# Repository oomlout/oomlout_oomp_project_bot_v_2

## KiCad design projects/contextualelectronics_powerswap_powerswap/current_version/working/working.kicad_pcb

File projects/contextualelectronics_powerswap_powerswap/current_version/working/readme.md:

# powerswap
 
## summary 
* id: contextualelectronics_powerswap_powerswap
* user: contextualelectronics
* name: powerswap
* board: powerswap
* repo: https://github.com/ContextualElectronics/PowerSwap
* src_file_repo_kicad_pcb: buck-boost/PowerSwap.kicad_pcb
* src_file_repo_kicad_pcb_link: https://github.com/ContextualElectronics/PowerSwap/tree/master/buck-boost/PowerSwap.kicad_pcb

* src_file_repo_brd: boost/Eagle/2015-10-22_20-31-01.brd
* src_file_repo_brd_link: https://github.com/ContextualElectronics/PowerSwap/tree/master/boost/Eagle/2015-10-22_20-31-01.brd
* src_file_repo_sch: buck-boost/PowerSwap.sch
* src_file_repo_sch_link: https://github.com/ContextualElectronics/PowerSwap/tree/master/buck-boost/PowerSwap.sch
* full details link: https://github.com/oomlout/oomlout_oomp_project_bot_v_2/tree/main/projects/contextualelectronics_powerswap_powerswap/current_version/working  

## schematic  
  
[schematic (pdf)](working_schematic.pdf) 

## pcb  

[board (pdf)](working.pdf)  

## working_bom
| Id | Designator | Footprint | Quantity | Designation | Supplier and ref |  | None | 
| --- | --- | --- | --- | --- | --- | --- | --- | 
| 1 | C1 | C_0805 | 1 | 4.7UF |  |  | [''] | 
| 2 | C2 | C_1210 | 1 | 22UF |  |  | [''] | 
| 3 | C3 | C_0805 | 1 | 0.1UF |  |  | [''] | 
| 4 | L1 | LQH3NPN2R2MM0L | 1 | 2.2uH |  |  | [''] | 
| 5 | P1,P2 | Pin_Header_Straight_1x02 | 2 | CONN_01X02 |  |  | [''] | 
| 6 | P3,P4,P5,P6 | Measurement_Point_Square-SMD-Pad_Small | 4 | TST |  |  | [''] | 
| 7 | R1 | R_0805 | 1 | 1.2M |  |  | [''] | 
| 8 | R2 | R_0805 | 1 | 215K |  |  | [''] | 
| 9 | R3,R4,R5 | R_0805 | 3 | 0 |  |  | [''] | 
| 10 | U1 | TPS63030 | 1 | TPS63030 |  |  | [''] | 
| 11 | G*** | PS_Logo | 1 | LOGO |  |  | [''] | 
| 12 | REF**1111,REF**1121,REF**1131,REF**1141,REF**1151,REF**1161,REF**1112,REF**1122,REF**1132,REF**1142,REF**1152,REF**1162,REF**1113,REF**1123,REF**1133,REF**1143,REF**1153,REF**1163,REF**1131,REF**1131,REF**1131,REF**1131,REF**1131,REF**1131,REF**1131,REF**111111,REF**111121,REF**111131,REF**111141,REF**111112,REF**111122,REF**111132,REF**111142,REF**111113,REF**111123,REF**111133,REF**111143,REF**111111,REF**111111,REF**111111,REF**111111,REF**111111,REF**111111,REF**11111111,REF**11111121,REF**11111131,REF**11111112,REF**11111122,REF**11111132,REF**11111113,REF**11111123,REF**11111133,REF**11111114,REF**11111124,REF**11111134 | VIA-0.6mm | 55 | VIA-0.6mm |  |  | [''] |

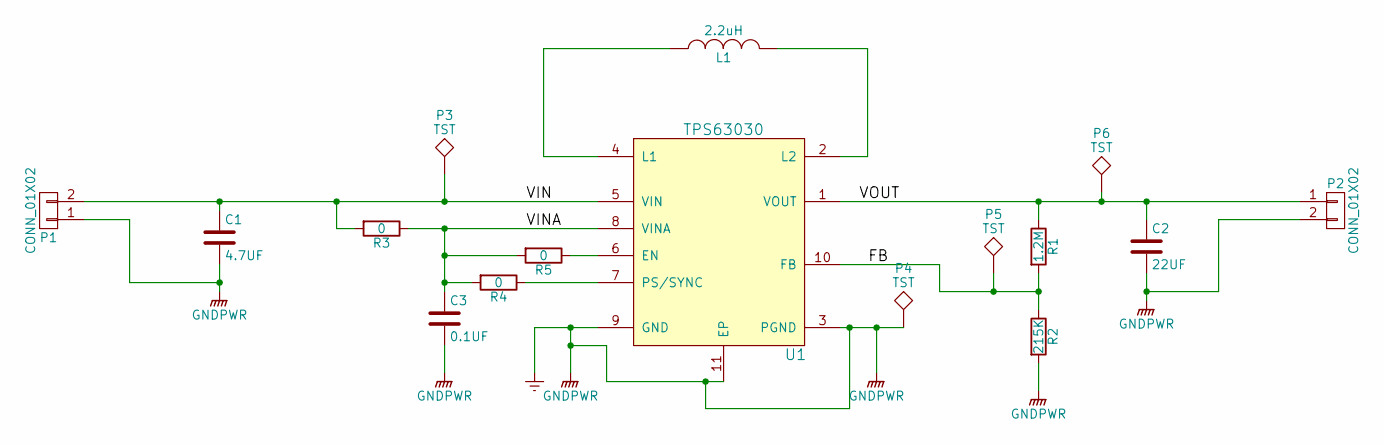
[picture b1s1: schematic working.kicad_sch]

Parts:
C1: 4.7UF; C_0805
C2: 22UF; C_1210
C3: 0.1UF; C_0805
L1: 2.2uH; LQH3NPN2R2MM0L; MPN LQH3NPN2R2MM0L
P1, P2: CONN_01X02; Pin_Header_Straight_1x02
P3, P4, P5, P6: TST; Measurement_Point_Square-SMD-Pad_Small
R1: 1.2M; R_0805
R2: 215K; R_0805
R3, R4, R5: 0; R_0805
U1: TPS63030

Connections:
/FB: P5.1, R1.2, R2.1, U1.10 (FB)
/VIN: C1.1, P1.2, P3.1, R3.2, U1.5 (VIN)
/VINA: C3.1, R3.1, R4.2, R5.2, U1.8 (VINA)
/VOUT: C2.1, P2.1, P6.1, R1.1, U1.1 (VOUT)
GNDPWR: C1.2, C2.2, C3.2, P1.1, P2.2, P4.1, R2.2, U1.3 (PGND), U1.9 (GND), U1.11 (EP)
unnamed: L1.1, U1.4 (L1)
unnamed: L1.2, U1.2 (L2)
unnamed: R4.1, U1.7 (PS/SYNC)
unnamed: R5.1, U1.6 (EN)

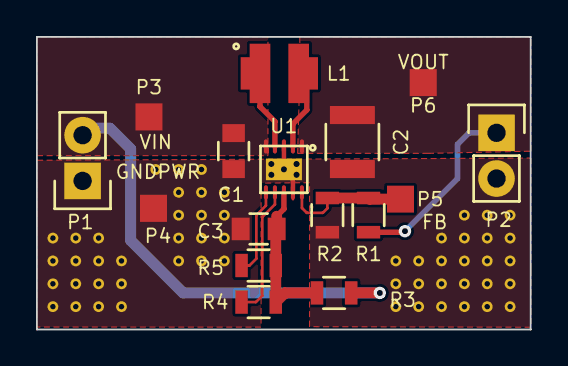
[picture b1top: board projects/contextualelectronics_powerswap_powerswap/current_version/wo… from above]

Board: 2 copper layers, 27.4 x 16.3 mm, 16 parts (0 on the bottom side), 9 nets.

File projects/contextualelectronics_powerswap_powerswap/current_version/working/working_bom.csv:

"Id";"Designator";"Footprint";"Quantity";"Designation";"Supplier and ref";
1;"C1";"C_0805";1;"4.7UF";;;
2;"C2";"C_1210";1;"22UF";;;
3;"C3";"C_0805";1;"0.1UF";;;
4;"L1";"LQH3NPN2R2MM0L";1;"2.2uH";;;
5;"P1,P2";"Pin_Header_Straight_1x02";2;"CONN_01X02";;;
6;"P3,P4,P5,P6";"Measurement_Point_Square-SMD-Pad_Small";4;"TST";;;
7;"R1";"R_0805";1;"1.2M";;;
8;"R2";"R_0805";1;"215K";;;
9;"R3,R4,R5";"R_0805";3;"0";;;
10;"U1";"TPS63030";1;"TPS63030";;;
11;"G***";"PS_Logo";1;"LOGO";;;
12;"REF**1111,REF**1121,REF**1131,REF**1141,REF**1151,REF**1161,REF**1112,REF**1122,REF**1132,REF**1142,REF**1152,REF**1162,REF**1113,REF**1123,REF**1133,REF**1143,REF**1153,REF**1163,REF**1131,REF**1131,REF**1131,REF**1131,REF**1131,REF**1131,REF**1131,REF**111111,REF**111121,REF**111131,REF**111141,REF**111112,REF**111122,REF**111132,REF**111142,REF**111113,REF**111123,REF**111133,REF**111143,REF**111111,REF**111111,REF**111111,REF**111111,REF**111111,REF**111111,REF**11111111,REF**11111121,REF**11111131,REF**11111112,REF**11111122,REF**11111132,REF**11111113,REF**11111123,REF**11111133,REF**11111114,REF**11111124,REF**11111134";"VIA-0.6mm";55;"VIA-0.6mm";;;

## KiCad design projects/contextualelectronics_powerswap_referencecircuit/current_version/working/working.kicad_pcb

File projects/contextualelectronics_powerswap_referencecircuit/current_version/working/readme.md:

# powerswap
 
## summary 
* id: contextualelectronics_powerswap_referencecircuit
* user: contextualelectronics
* name: powerswap
* board: referencecircuit
* repo: https://github.com/ContextualElectronics/PowerSwap
* src_file_repo_kicad_pcb: boost/Boost.kicad_pcb
* src_file_repo_kicad_pcb_link: https://github.com/ContextualElectronics/PowerSwap/tree/master/boost/Boost.kicad_pcb

* src_file_repo_brd: boost/Eagle/2015-10-22_20-31-01.brd
* src_file_repo_brd_link: https://github.com/ContextualElectronics/PowerSwap/tree/master/boost/Eagle/2015-10-22_20-31-01.brd
* src_file_repo_sch: boost/Boost.sch
* src_file_repo_sch_link: https://github.com/ContextualElectronics/PowerSwap/tree/master/boost/Boost.sch
* full details link: https://github.com/oomlout/oomlout_oomp_project_bot_v_2/tree/main/projects/contextualelectronics_powerswap_referencecircuit/current_version/working  

## schematic  
  
[schematic (pdf)](working_schematic.pdf) 

## pcb  

[board (pdf)](working.pdf)  

## working_bom
| Id | Designator | Footprint | Quantity | Designation | Supplier and ref |  | None | 
| --- | --- | --- | --- | --- | --- | --- | --- | 
| 1 | C1,C2,C6,C7,C8,C9 | C_1206_HandSoldering | 6 | 10U |  |  | [''] | 
| 2 | C3 | C_0805_HandSoldering | 1 | 1U |  |  | [''] | 
| 3 | C4 | C_0805_HandSoldering | 1 | 100nF |  |  | [''] | 
| 4 | C5 | C_0805_HandSoldering | 1 | 820pF |  |  | [''] | 
| 5 | D1 | SMA-SMB_Universal_Handsoldering | 1 | B340LA-13-F |  |  | [''] | 
| 6 | L1 | SRU1048 | 1 | SRU1048 |  |  | [''] | 
| 7 | P1,P2 | Pin_Header_Straight_1x02 | 2 | CONN_01X02 |  |  | [''] | 
| 8 | R1 | R_0805_HandSoldering | 1 | 57K6 |  |  | [''] | 
| 9 | R2 | R_0805_HandSoldering | 1 | 150K |  |  | [''] | 
| 10 | R3 | R_0805_HandSoldering | 1 | 39K |  |  | [''] | 
| 11 | TP1,TP2 | Measurement_Point_Square-SMD-Pad_Big | 2 | CONN_01X01 |  |  | [''] | 
| 12 | U1 | TPS61087 | 1 | TPS61087 |  |  | [''] | 
| 13 | REF**111121,REF**111131,REF**111122,REF**111132,REF**111123,REF**111133,REF**1111111,REF**1111121,REF**1111131,REF**1111112,REF**1111122,REF**1111132,REF**1111113,REF**1111123,REF**1111133,REF**1111114,REF**1111124,REF**1111134,REF**1111115,REF**1111125,REF**1111135,REF**1111116,REF**1111126,REF**1111136,REF**1111127,REF**1111137,REF**1111128,REF**1111138,REF**1111111,REF**1111113,REF**1111112,REF**1111116,REF**1111115,REF**1111114 | STITCH-VIA | 34 | STITCH-VIA |  |  | [''] | 
| 14 | REF**,REF**,REF**,REF** | MountingHole_3mm | 4 | MountingHole_3mm |  |  | [''] | 
| 15 | D2 | LED-0805 | 1 | LED |  |  | [''] | 
| 16 | R4 | R_0805_HandSoldering | 1 | 500 |  |  | [''] | 
| 17 | G*** | PS | 1 | LOGO |  |  | [''] | 

## bom_schematic
no data

## mounting_holes
| x | y | package | value | ref | size | 
| --- | --- | --- | --- | --- | --- | 
| 0.25 | 0.0 | MountingHole_3mm | MountingHole_3mm | REF** | m3 | 
| 0.0 | 42.93 | MountingHole_3mm | MountingHole_3mm | REF** | m3 | 
| 22.86 | 42.93 | MountingHole_3mm | MountingHole_3mm | REF** | m3 | 
| 22.86 | 0.0 | MountingHole_3mm | MountingHole_3mm | REF** | m3 |

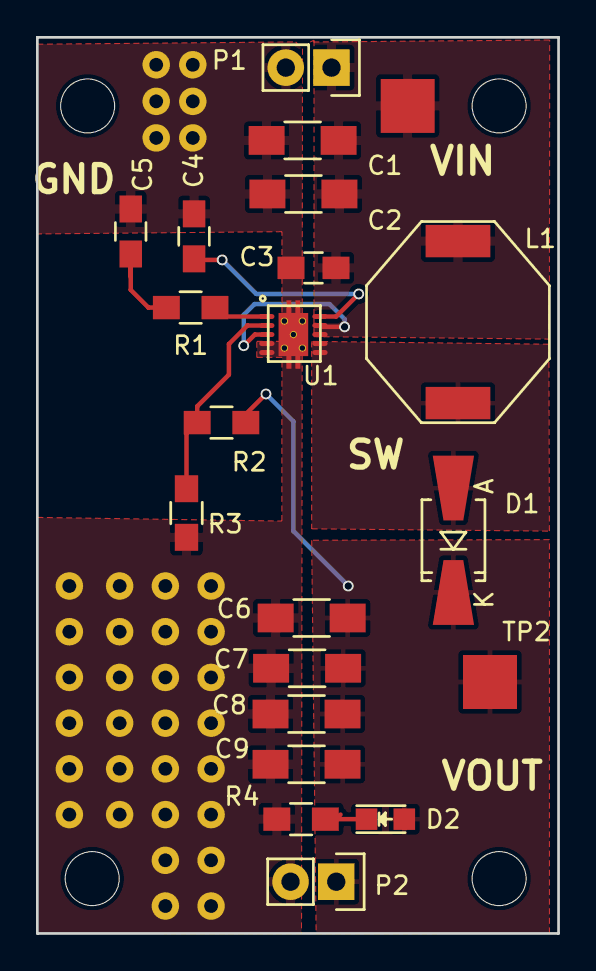
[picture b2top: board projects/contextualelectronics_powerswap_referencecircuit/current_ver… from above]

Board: 2 copper layers, 29.0 x 49.8 mm, 21 parts (0 on the bottom side), 9 nets.

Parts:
C1, C2, C6, C7, C8, C9: 10U; C_1206_HandSoldering
C3: 1U; C_0805_HandSoldering
C4: 100nF; C_0805_HandSoldering
C5: 820pF; C_0805_HandSoldering
D1: B340LA-13-F; SMA-SMB_Universal_Handsoldering
D2: LED; LED-0805
L1: SRU1048
P1, P2: CONN_01X02; Pin_Header_Straight_1x02
R1: 57K6; R_0805_HandSoldering
R2: 150K; R_0805_HandSoldering
R3: 39K; R_0805_HandSoldering
R4: 500; R_0805_HandSoldering
TP1, TP2: CONN_01X01; Measurement_Point_Square-SMD-Pad_Big
U1: TPS61087

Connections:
/SW: D1.2, L1.2, U1.6, U1.7
/Vin: C1.1, C2.1, C3.1, L1.1, P1.1, TP1.1, U1.3, U1.8, U1.9
/Vout: C6.1, C7.1, C8.1, C9.1, D1.1, D2.2, P2.1, R2.1, TP2.1
GND: C1.2, C2.2, C3.2, C4.2, C5.2, C6.2, C7.2, C8.2, C9.2, P1.2, P2.2, R3.2, R4.2, U1.4, U1.5, U1.11
unnamed: C4.1, U1.10
unnamed: C5.1, R1.2
unnamed: D2.1, R4.1
unnamed: R1.1, U1.1
unnamed: R2.2, R3.1, U1.2

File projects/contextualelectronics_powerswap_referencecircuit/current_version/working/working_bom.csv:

"Id";"Designator";"Footprint";"Quantity";"Designation";"Supplier and ref";
1;"C1,C2,C6,C7,C8,C9";"C_1206_HandSoldering";6;"10U";;;
2;"C3";"C_0805_HandSoldering";1;"1U";;;
3;"C4";"C_0805_HandSoldering";1;"100nF";;;
4;"C5";"C_0805_HandSoldering";1;"820pF";;;
5;"D1";"SMA-SMB_Universal_Handsoldering";1;"B340LA-13-F";;;
6;"L1";"SRU1048";1;"SRU1048";;;
7;"P1,P2";"Pin_Header_Straight_1x02";2;"CONN_01X02";;;
8;"R1";"R_0805_HandSoldering";1;"57K6";;;
9;"R2";"R_0805_HandSoldering";1;"150K";;;
10;"R3";"R_0805_HandSoldering";1;"39K";;;
11;"TP1,TP2";"Measurement_Point_Square-SMD-Pad_Big";2;"CONN_01X01";;;
12;"U1";"TPS61087";1;"TPS61087";;;
13;"REF**111121,REF**111131,REF**111122,REF**111132,REF**111123,REF**111133,REF**1111111,REF**1111121,REF**1111131,REF**1111112,REF**1111122,REF**1111132,REF**1111113,REF**1111123,REF**1111133,REF**1111114,REF**1111124,REF**1111134,REF**1111115,REF**1111125,REF**1111135,REF**1111116,REF**1111126,REF**1111136,REF**1111127,REF**1111137,REF**1111128,REF**1111138,REF**1111111,REF**1111113,REF**1111112,REF**1111116,REF**1111115,REF**1111114";"STITCH-VIA";34;"STITCH-VIA";;;
14;"REF**,REF**,REF**,REF**";"MountingHole_3mm";4;"MountingHole_3mm";;;
15;"D2";"LED-0805";1;"LED";;;
16;"R4";"R_0805_HandSoldering";1;"500";;;
17;"G***";"PS";1;"LOGO";;;

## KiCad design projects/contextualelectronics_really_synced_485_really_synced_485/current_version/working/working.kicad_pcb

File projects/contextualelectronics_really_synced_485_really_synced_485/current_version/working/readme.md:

# really_synced_485
 
## summary 
* id: contextualelectronics_really_synced_485_really_synced_485
* user: contextualelectronics
* name: really_synced_485
* board: really_synced_485
* repo: https://github.com/ContextualElectronics/Really-Synced-485
* src_file_repo_kicad_pcb: Really Synced 485.kicad_pcb
* src_file_repo_kicad_pcb_link: https://github.com/ContextualElectronics/Really-Synced-485/tree/master/Really Synced 485.kicad_pcb

* src_file_repo_sch: Really Synced 485.sch
* src_file_repo_sch_link: https://github.com/ContextualElectronics/Really-Synced-485/tree/master/Really Synced 485.sch
* full details link: https://github.com/oomlout/oomlout_oomp_project_bot_v_2/tree/main/projects/contextualelectronics_really_synced_485_really_synced_485/current_version/working  

## schematic  
  
[schematic (pdf)](working_schematic.pdf) 

## pcb  

[board (pdf)](working.pdf)  

## working_bom
| Id | Designator | Footprint | Quantity | Designation | Supplier and ref |  | None | 
| --- | --- | --- | --- | --- | --- | --- | --- | 
| 1 | D1,D2,D3,D4,D5 | LED_0805 | 5 | LED |  |  | [''] | 
| 2 | J1 | 195-4MST | 1 | CONN_02X04 |  |  | [''] | 
| 3 | J2,J3 | Pin_Header_Straight_1x03_Pitch2.54mm | 2 | CONN_01X03 |  |  | [''] | 
| 4 | J4 | 54602-908LF | 1 | CONN_02X04 |  |  | [''] | 
| 5 | R12,R15,R13,R14 | R_0805_HandSoldering | 4 | NOPE |  |  | [''] | 
| 6 | U1 | CE_Header | 1 | CE_HEADER |  |  | [''] | 
| 7 | U2 | SOIC-8_3.9x4.9mm_Pitch1.27mm | 1 | SN75179B |  |  | [''] | 
| 8 | U3 | SOIC-8_3.9x4.9mm_Pitch1.27mm | 1 | SN65HVD82 |  |  | [''] | 
| 9 | C1,C2 | C_0805 | 2 | .1U |  |  | [''] | 
| 10 | R1,R4,R7,R8,R9 | R_0805_HandSoldering | 5 | 220 |  |  | [''] | 
| 11 | R2,R3,R5,R6 | R_0805_HandSoldering | 4 | 5K |  |  | [''] | 
| 12 | R10,R11 | R_0805_HandSoldering | 2 | 120 |  |  | [''] | 
| 13 | R16,R18 | R_0805_HandSoldering | 2 | 375 |  |  | [''] | 
| 14 | R17 | R_0805_HandSoldering | 1 | 60 |  |  | [''] | 
| 15 | R19,R20 | R_0805_HandSoldering | 2 | 0 |  |  | [''] | 

## bom_schematic
| Ref | Qnty | Value | Cmp name | Footprint | Description | Vendor | DNP | 
| --- | --- | --- | --- | --- | --- | --- | --- | 
| C1, C2 | 2 | .1U | C | Capacitors_SMD:C_0805 |  |  |  | 
| D1, D2, D3, D4, D5 | 5 | LED | LED | LEDs:LED_0805 |  |  |  | 
| J1 | 1 | CONN_02X04 | CONN_02X04 | ReallySynced:195-4MST |  |  |  | 
| J2, J3 | 2 | CONN_01X03 | CONN_01X03 | Pin_Headers:Pin_Header_Straight_1x03_Pitch2.54mm |  |  |  | 
| J4 | 1 | CONN_02X04 | CONN_02X04 | ReallySynced:54602-908LF |  |  |  | 
| R1, R4, R7, R8, R9 | 5 | 220 | R | Resistors_SMD:R_0805_HandSoldering |  |  |  | 
| R2, R3, R5, R6 | 4 | 5K | R | Resistors_SMD:R_0805_HandSoldering |  |  |  | 
| R10, R11 | 2 | 120 | R | Resistors_SMD:R_0805_HandSoldering |  |  |  | 
| R12, R13, R14, R15 | 4 | NOPE | R | Resistors_SMD:R_0805_HandSoldering |  |  |  | 
| R16, R18 | 2 | 375 | R | Resistors_SMD:R_0805_HandSoldering |  |  |  | 
| R17 | 1 | 60 | R | Resistors_SMD:R_0805_HandSoldering |  |  |  | 
| R19, R20 | 2 | 0 | R | Resistors_SMD:R_0805_HandSoldering |  |  |  | 
| U1 | 1 | CE_HEADER | CE_HEADER | ReallySynced:CE_Header |  |  |  | 
| U2 | 1 | SN75179B | SN75179B | Housings_SOIC:SOIC-8_3.9x4.9mm_Pitch1.27mm |  |  |  | 
| U3 | 1 | SN65HVD82 | SN65HVD82 | Housings_SOIC:SOIC-8_3.9x4.9mm_Pitch1.27mm |  |  |  |

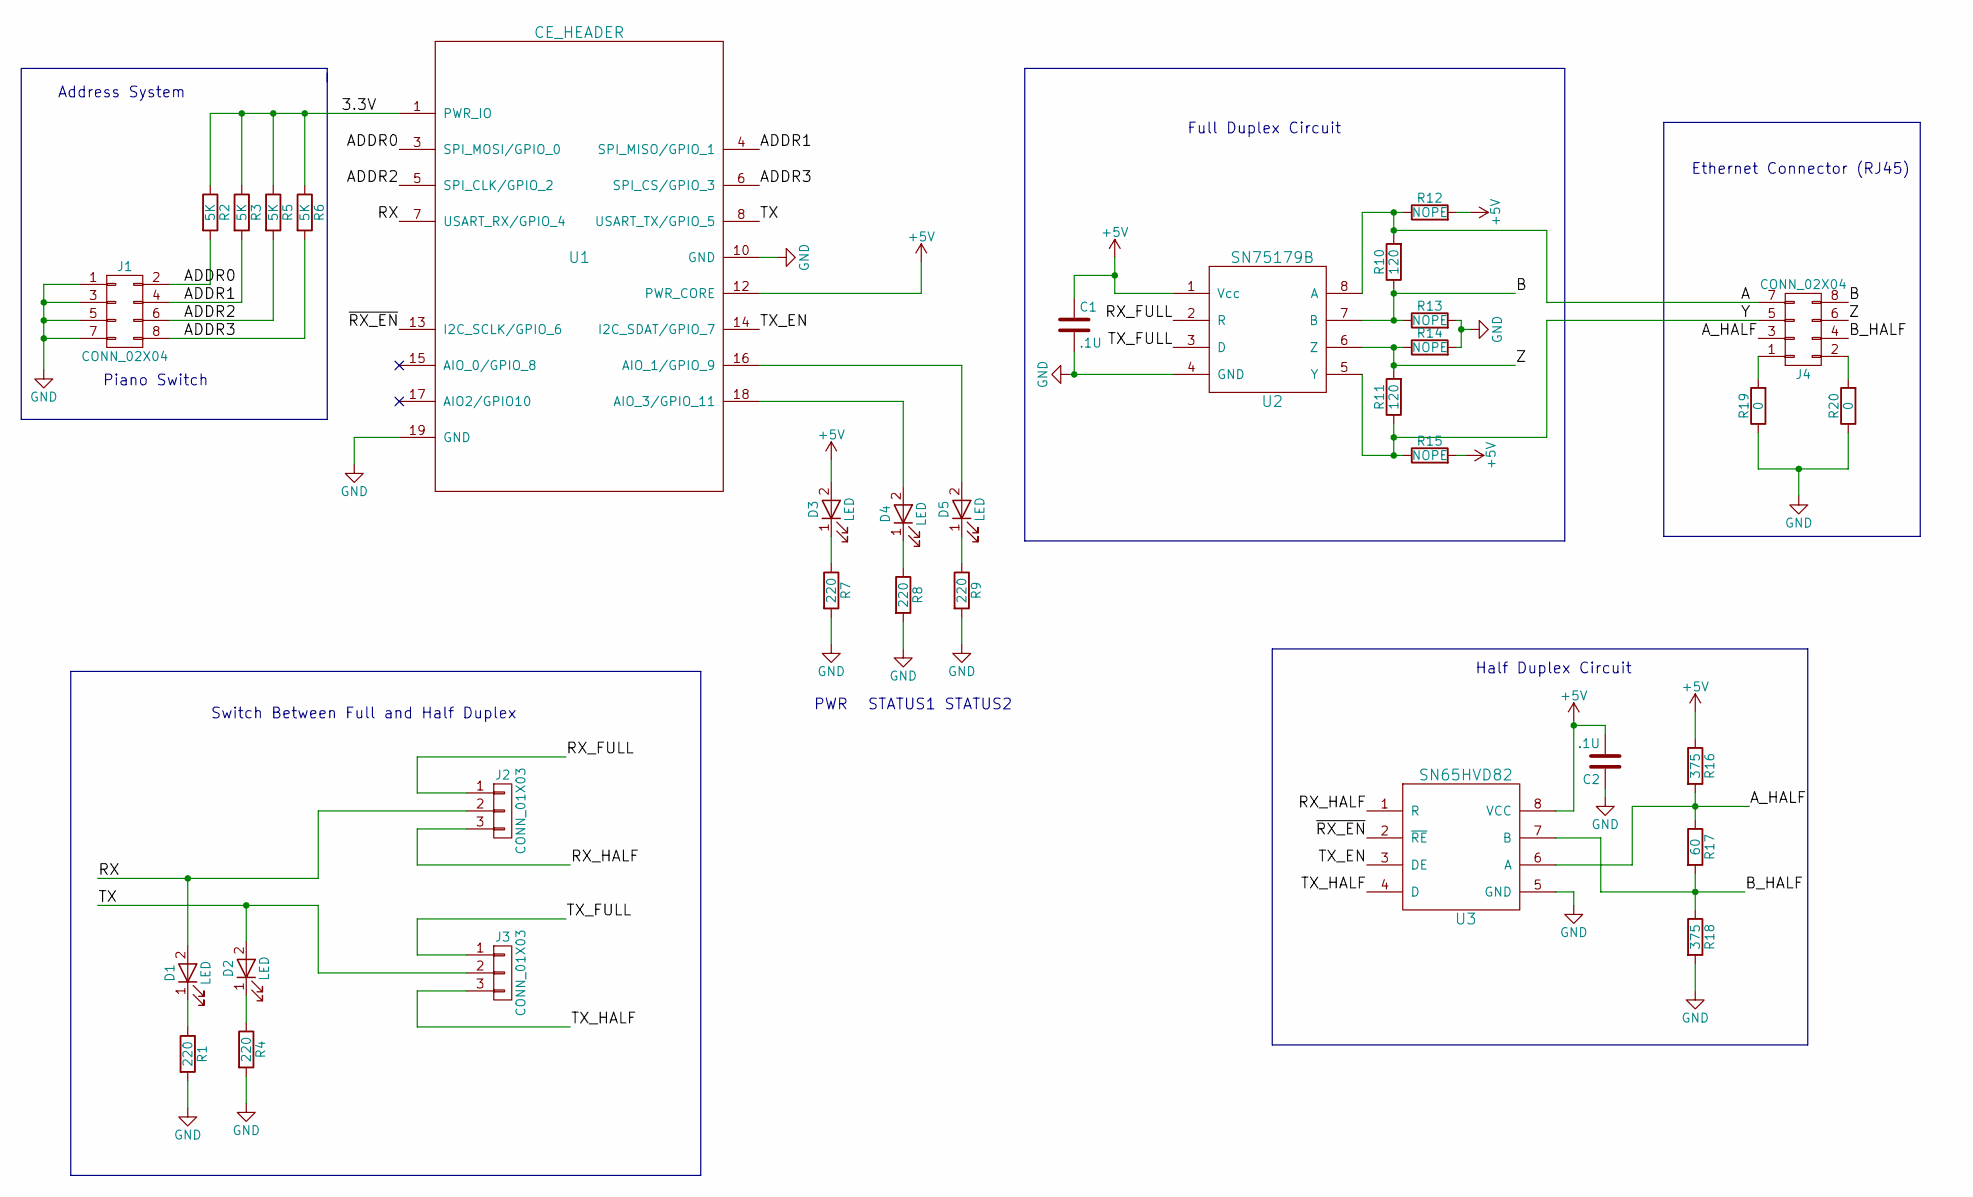
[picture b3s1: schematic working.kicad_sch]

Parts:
C1, C2: .1U; C_0805
D1, D2, D3, D4, D5: LED; LED_0805
J1: CONN_02X04; 195-4MST; MPN 195-4MST
J2, J3: CONN_01X03; Pin_Header_Straight_1x03_Pitch2.54mm
J4: CONN_02X04; 54602-908LF; MPN 54602-908LF
R1, R4, R7, R8, R9: 220; R_0805_HandSoldering
R2, R3, R5, R6: 5K; R_0805_HandSoldering
R10, R11: 120; R_0805_HandSoldering
R12, R13, R14, R15: NOPE; R_0805_HandSoldering
R16, R18: 375; R_0805_HandSoldering
R17: 60; R_0805_HandSoldering
R19, R20: 0; R_0805_HandSoldering
U1: CE_HEADER; CE_Header
U2: SN75179B; SOIC-8_3.9x4.9mm_Pitch1.27mm; MPN SN75179BDR
U3: SN65HVD82; SOIC-8_3.9x4.9mm_Pitch1.27mm; MPN SN65HVD82DR

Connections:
+5V: C1.1, C2.2, D3.2 (A), R12.2, R15.2, R16.1, U1.12 (PWR_CORE), U2.1 (Vcc), U3.8 (VCC)
/3.3V: R2.1, R3.1, R5.1, R6.1, U1.1 (PWR_IO)
/A: J4.7, R10.2, R12.1, U2.8 (A)
/ADDR0: J1.2, R2.2, U1.3 (SPI_MOSI/GPIO_0)
/ADDR1: J1.4, R3.2, U1.4 (SPI_MISO/GPIO_1)
/ADDR2: J1.6, R5.2, U1.5 (SPI_CLK/GPIO_2)
/ADDR3: J1.8, R6.2, U1.6 (SPI_CS/GPIO_3)
/A_HALF: J4.3, R16.2, R17.1, U3.6 (A)
/B: J4.8, R10.1, R13.1, U2.7 (B)
/B_HALF: J4.4, R17.2, R18.1, U3.7 (B)
/RX: D1.2 (A), J2.2, U1.7 (USART_RX/GPIO_4)
/RX_FULL: J2.1, U2.2 (R)
/RX_HALF: J2.3, U3.1 (R)
/TX: D2.2 (A), J3.2, U1.8 (USART_TX/GPIO_5)
/TX_EN: U1.14 (I2C_SDAT/GPIO_7), U3.3 (DE)
/TX_FULL: J3.1, U2.3 (D)
/TX_HALF: J3.3, U3.4 (D)
/Y: J4.5, R11.1, R15.1, U2.5 (Y)
/Z: J4.6, R11.2, R14.1, U2.6 (Z)
/~RX_EN: U1.13 (I2C_SCLK/GPIO_6), U3.2 (~RE)
GND: C1.2, C2.1, J1.1, J1.3, J1.5, J1.7, R1.2, R4.2, R7.2, R8.2, R9.2, R13.2, R14.2, R18.2, R19.1, R20.1, U1.10 (GND), U1.19 (GND), U2.4 (GND), U3.5 (GND)
unnamed: D1.1 (K), R1.1
unnamed: D2.1 (K), R4.1
unnamed: D3.1 (K), R7.1
unnamed: D4.1 (K), R8.1
unnamed: D4.2 (A), U1.18 (AIO_3/GPIO_11)
unnamed: D5.1 (K), R9.1
unnamed: D5.2 (A), U1.16 (AIO_1/GPIO_9)
unnamed: J4.1, R19.2
unnamed: J4.2, R20.2

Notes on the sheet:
STATUS2
STATUS1
Full Duplex Circuit
Address System
Ethernet Connector (RJ45)
Half Duplex Circuit
Switch Between Full and Half Duplex
PWR
Piano Switch

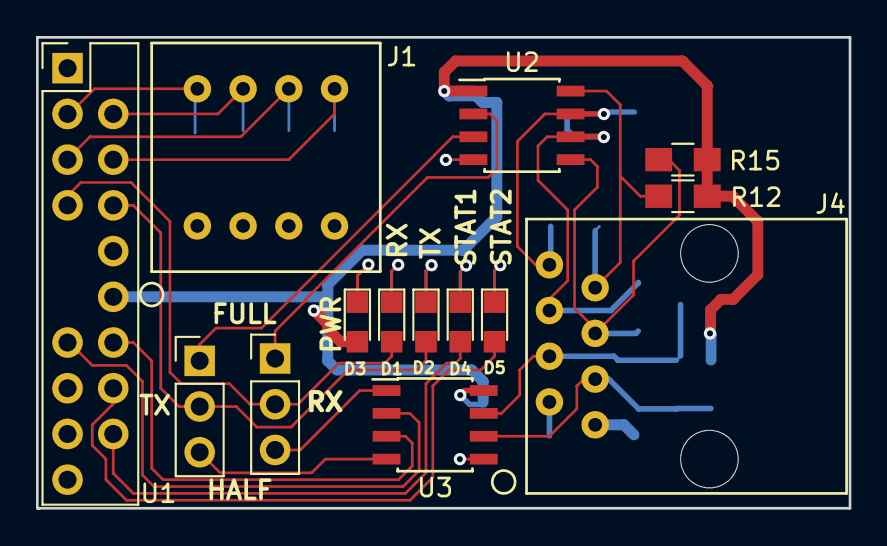
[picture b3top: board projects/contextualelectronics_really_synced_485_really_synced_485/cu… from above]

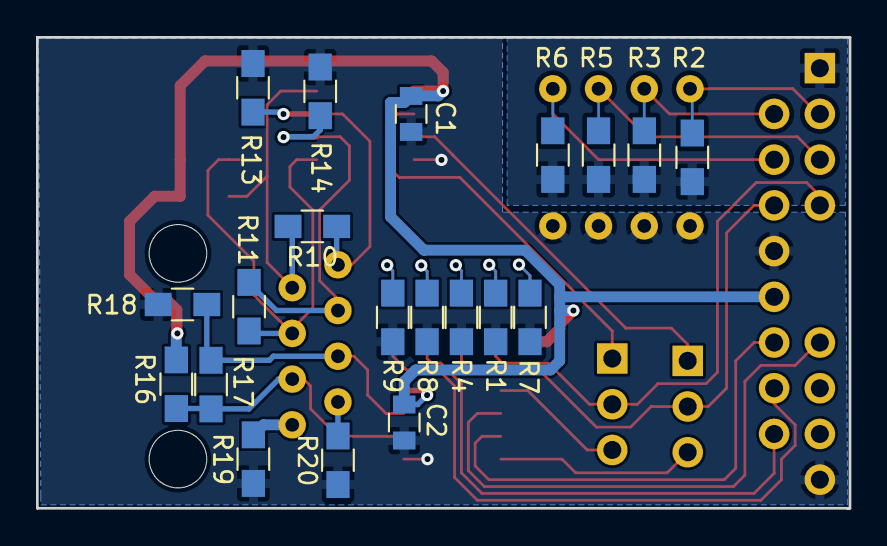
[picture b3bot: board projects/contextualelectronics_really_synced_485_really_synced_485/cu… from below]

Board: 2 copper layers, 45.1 x 26.2 mm, 34 parts (20 on the bottom side), 30 nets.

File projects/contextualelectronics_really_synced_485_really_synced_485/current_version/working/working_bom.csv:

"Id";"Designator";"Footprint";"Quantity";"Designation";"Supplier and ref";
1;"D1,D2,D3,D4,D5";"LED_0805";5;"LED";;;
2;"J1";"195-4MST";1;"CONN_02X04";;;
3;"J2,J3";"Pin_Header_Straight_1x03_Pitch2.54mm";2;"CONN_01X03";;;
4;"J4";"54602-908LF";1;"CONN_02X04";;;
5;"R12,R15,R13,R14";"R_0805_HandSoldering";4;"NOPE";;;
6;"U1";"CE_Header";1;"CE_HEADER";;;
7;"U2";"SOIC-8_3.9x4.9mm_Pitch1.27mm";1;"SN75179B";;;
8;"U3";"SOIC-8_3.9x4.9mm_Pitch1.27mm";1;"SN65HVD82";;;
9;"C1,C2";"C_0805";2;".1U";;;
10;"R1,R4,R7,R8,R9";"R_0805_HandSoldering";5;"220";;;
11;"R2,R3,R5,R6";"R_0805_HandSoldering";4;"5K";;;
12;"R10,R11";"R_0805_HandSoldering";2;"120";;;
13;"R16,R18";"R_0805_HandSoldering";2;"375";;;
14;"R17";"R_0805_HandSoldering";1;"60";;;
15;"R19,R20";"R_0805_HandSoldering";2;"0";;;

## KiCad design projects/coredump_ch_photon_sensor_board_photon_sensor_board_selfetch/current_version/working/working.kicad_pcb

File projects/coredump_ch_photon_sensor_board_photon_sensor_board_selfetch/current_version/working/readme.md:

# photon_sensor_board
 
## summary 
* id: coredump_ch_photon_sensor_board_photon_sensor_board_selfetch
* user: coredump_ch
* name: photon_sensor_board
* board: photon_sensor_board_selfetch
* repo: https://github.com/coredump-ch/photon-sensor-board
* src_file_repo_kicad_pcb: photon-sensor-board-selfetch.kicad_pcb
* src_file_repo_kicad_pcb_link: https://github.com/coredump-ch/photon-sensor-board/tree/master/photon-sensor-board-selfetch.kicad_pcb

* src_file_repo_sch: 
* src_file_repo_sch_link: https://github.com/coredump-ch/photon-sensor-board/tree/master/
* full details link: https://github.com/oomlout/oomlout_oomp_project_bot_v_2/tree/main/projects/coredump_ch_photon_sensor_board_photon_sensor_board_selfetch/current_version/working

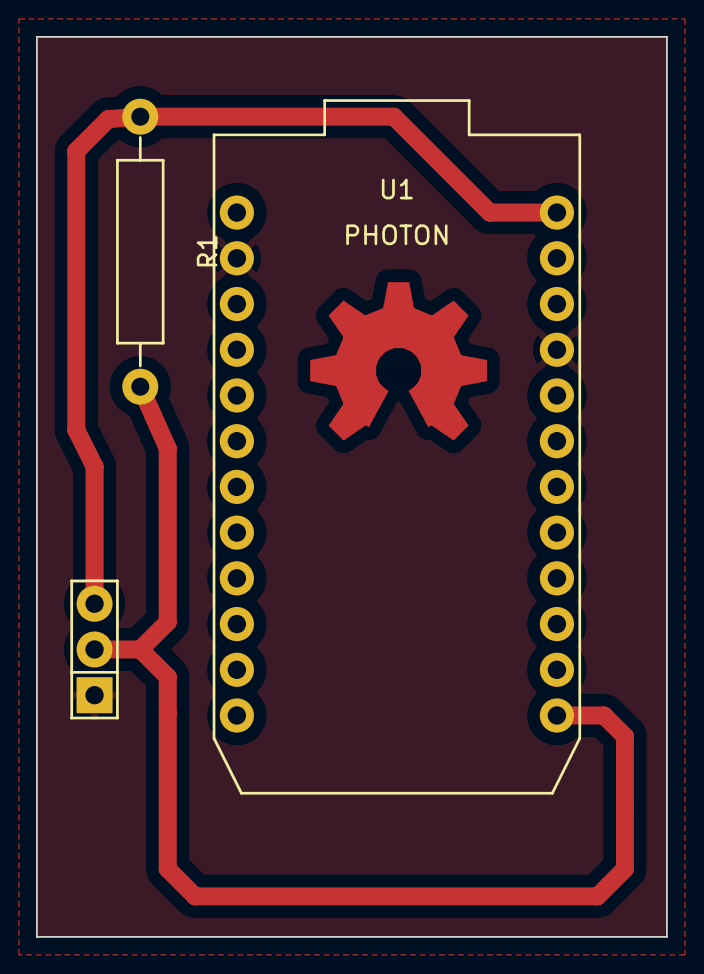
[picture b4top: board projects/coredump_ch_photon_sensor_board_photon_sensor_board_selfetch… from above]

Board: 2 copper layers, 35.0 x 50.0 mm, 4 parts (0 on the bottom side), 3 nets.

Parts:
OSHW_LOGO: oshw-copper-10
R1: 4.7kΩ; Resistor_Horizontal_RM15mm
U1: PHOTON; photon
U2: DS18B20; PIN_ARRAY_3X1

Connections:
GND: U1.2, U1.21, U2.1
unnamed: R1.1, U1.24, U2.3
unnamed: R1.2, U1.13, U2.2

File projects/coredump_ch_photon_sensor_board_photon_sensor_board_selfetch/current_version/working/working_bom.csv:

"Id";"Designator";"Footprint";"Quantity";"Designation";"Supplier and ref";
1;"R1";"Resistor_Horizontal_RM15mm";1;"4.7kΩ";;;
2;"U2";"PIN_ARRAY_3X1";1;"DS18B20";;;
3;"U1";"photon";1;"PHOTON";;;
4;"OSHW_LOGO";"oshw-copper-10";1;"";;;

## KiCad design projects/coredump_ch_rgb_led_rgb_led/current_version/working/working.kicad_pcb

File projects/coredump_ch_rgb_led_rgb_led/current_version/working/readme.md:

# rgb_led
 
## summary 
* id: coredump_ch_rgb_led_rgb_led
* user: coredump_ch
* name: rgb_led
* board: rgb_led
* repo: https://github.com/coredump-ch/rgb-led
* src_file_repo_kicad_pcb: v1/pcb/rgb_led.kicad_pcb
* src_file_repo_kicad_pcb_link: https://github.com/coredump-ch/rgb-led/tree/master/v1/pcb/rgb_led.kicad_pcb

* src_file_repo_sch: v1/pcb/rgb_led.sch
* src_file_repo_sch_link: https://github.com/coredump-ch/rgb-led/tree/master/v1/pcb/rgb_led.sch
* full details link: https://github.com/oomlout/oomlout_oomp_project_bot_v_2/tree/main/projects/coredump_ch_rgb_led_rgb_led/current_version/working

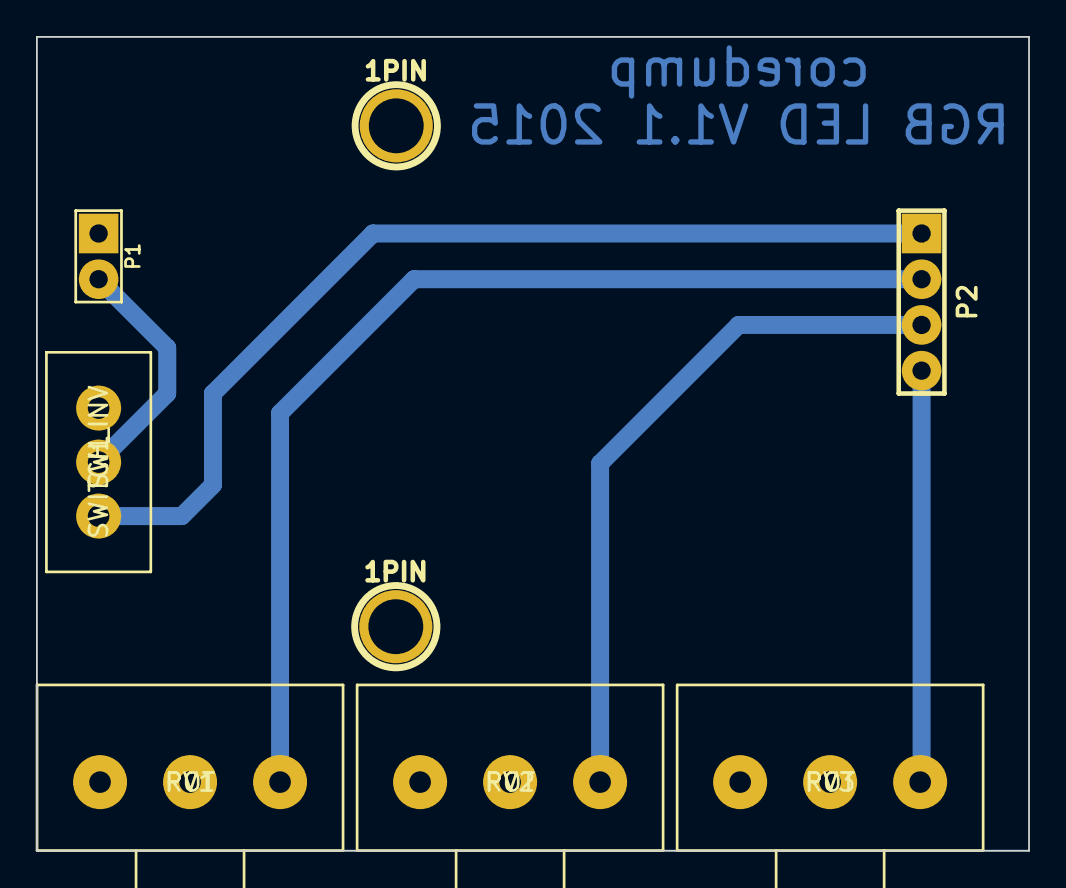
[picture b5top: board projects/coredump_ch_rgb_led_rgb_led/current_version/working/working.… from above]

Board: 2 copper layers, 55.1 x 45.2 mm, 8 parts (0 on the bottom side), 6 nets.

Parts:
1PIN, 1PIN#2: P***; 1pin
P1: CONN_2; PIN_ARRAY_2X1_THICK
P2: CONN_4; PIN_ARRAY_4x1_THICK
RV1, RV2, RV3: POT; POT_3_THICK
SW1: SWITCH_INV; Switch_SS-12F46

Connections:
GND: P1.1, RV1.1, RV1.2, RV2.1, RV2.2, RV3.1, RV3.2
unnamed: P2.4, RV3.3
unnamed: P2.3, RV2.3
unnamed: P2.2, RV1.3
unnamed: P2.1, SW1.1
VDD: P1.2, SW1.2

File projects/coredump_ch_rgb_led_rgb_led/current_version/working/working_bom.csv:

"Id";"Designator";"Footprint";"Quantity";"Designation";"Supplier and ref";
1;"RV2,RV3,RV1";"POT_3_THICK";3;"POT";;;
2;"P2";"PIN_ARRAY_4x1_THICK";1;"CONN_4";;;
3;"P1";"PIN_ARRAY_2X1_THICK";1;"CONN_2";;;
4;"1PIN,1PIN";"1pin";2;"P***";;;
5;"SW1";"Switch_SS-12F46";1;"SWITCH_INV";;;
6;"";"OSHW_COPPER_10MM";1;"";;;

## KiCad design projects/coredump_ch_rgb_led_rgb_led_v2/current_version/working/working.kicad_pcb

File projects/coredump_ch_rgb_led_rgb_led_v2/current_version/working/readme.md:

# rgb_led
 
## summary 
* id: coredump_ch_rgb_led_rgb_led_v2
* user: coredump_ch
* name: rgb_led
* board: rgb_led_v2
* repo: https://github.com/coredump-ch/rgb-led
* src_file_repo_kicad_pcb: v2/pcb-v2.2/rgb-led-v2.kicad_pcb
* src_file_repo_kicad_pcb_link: https://github.com/coredump-ch/rgb-led/tree/master/v2/pcb-v2.2/rgb-led-v2.kicad_pcb

* src_file_repo_sch: v2/pcb-v2.2/rgb-led-v2.sch
* src_file_repo_sch_link: https://github.com/coredump-ch/rgb-led/tree/master/v2/pcb-v2.2/rgb-led-v2.sch
* full details link: https://github.com/oomlout/oomlout_oomp_project_bot_v_2/tree/main/projects/coredump_ch_rgb_led_rgb_led_v2/current_version/working

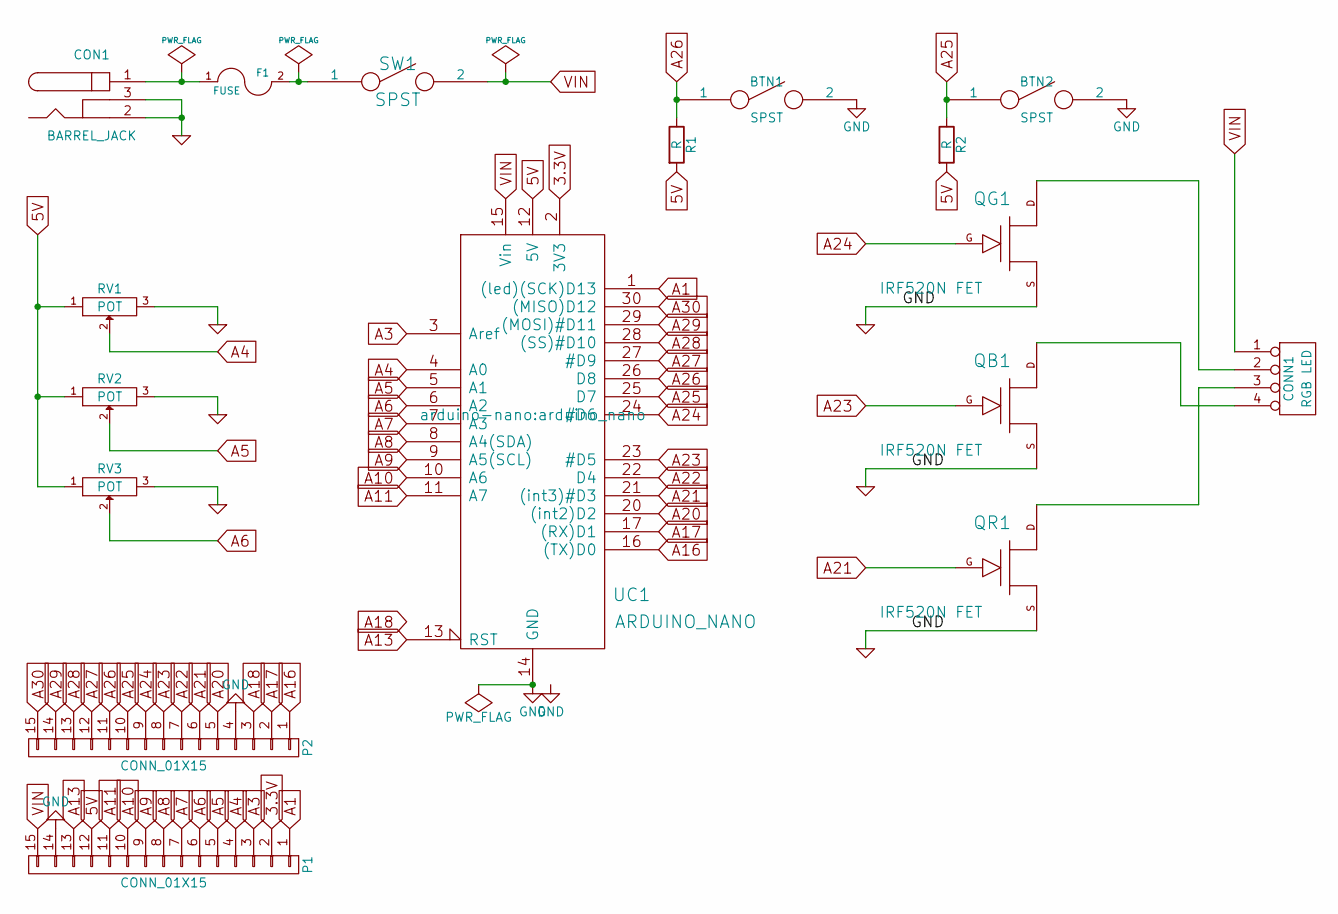
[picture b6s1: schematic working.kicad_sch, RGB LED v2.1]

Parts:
BTN1, BTN2: SPST; PUSHBUTTON_TS044S
CON1: BARREL_JACK
CONN1: RGB LED; PIN_ARRAY_4x1_THICK
F1: FUSE; KCD3
P1, P2: CONN_01X15; Pin_Header_Straight_1x15_Pitch2.54mm
QB1: IRF520N FET; IRF520N
QG1: IRF520N FET; IRF520N
QR1: IRF520N FET; IRF520N
R1, R2: R; R_Axial_DIN0207_L6.3mm_D2.5mm_P10.16mm_Horizontal
RV1, RV2, RV3: POT; POT_3
SW1: SPST; Switch_SS-12F46
UC1: ARDUINO_NANO; arduino_nano

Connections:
3.3V: P1.2, UC1.2 (3V3)
5V: P1.12, R1.2, R2.2, RV1.1, RV2.1, RV3.1, UC1.12 (5V)
A1: P1.1, UC1.1 ((led)(SCK)D13)
A3: P1.3, UC1.3 (Aref)
A4: P1.4, RV1.2, UC1.4 (A0)
A5: P1.5, RV2.2, UC1.5 (A1)
A6: P1.6, RV3.2, UC1.6 (A2)
A7: P1.7, UC1.7 (A3)
A8: P1.8, UC1.8 (A4(SDA))
A9: P1.9, UC1.9 (A5(SCL))
A10: P1.10, UC1.10 (A6)
A11: P1.11, UC1.11 (A7)
A13: P1.13, UC1.13 (RST)
A16: P2.1, UC1.16 ((TX)D0)
A17: P2.2, UC1.17 ((RX)D1)
A18: P2.3, UC1.18 (RST)
A20: P2.5, UC1.20 ((int2)D2)
A21: P2.6, QR1.G, UC1.21 ((int3)#D3)
A22: P2.7, UC1.22 (D4)
A23: P2.8, QB1.G, UC1.23 (#D5)
A24: P2.9, QG1.G, UC1.24 (#D6)
A25: BTN2.1, P2.10, R2.1, UC1.25 (D7)
A26: BTN1.1, P2.11, R1.1, UC1.26 (D8)
A27: P2.12, UC1.27 (#D9)
A28: P2.13, UC1.28 ((SS)#D10)
A29: P2.14, UC1.29 ((MOSI)#D11)
A30: P2.15, UC1.30 ((MISO)D12)
GND: BTN1.2, BTN2.2, CON1.2, CON1.3, P1.14, P2.4, QB1.S, QG1.S, QR1.S, RV1.3, RV2.3, RV3.3, UC1.14 (GND), UC1.19 (GND)
unnamed: CON1.1, F1.1
unnamed: CONN1.2, QG1.D
unnamed: CONN1.3, QR1.D
unnamed: CONN1.4, QB1.D
unnamed: F1.2, SW1.1
VIN: CONN1.1, P1.15, SW1.2, UC1.15 (Vin)

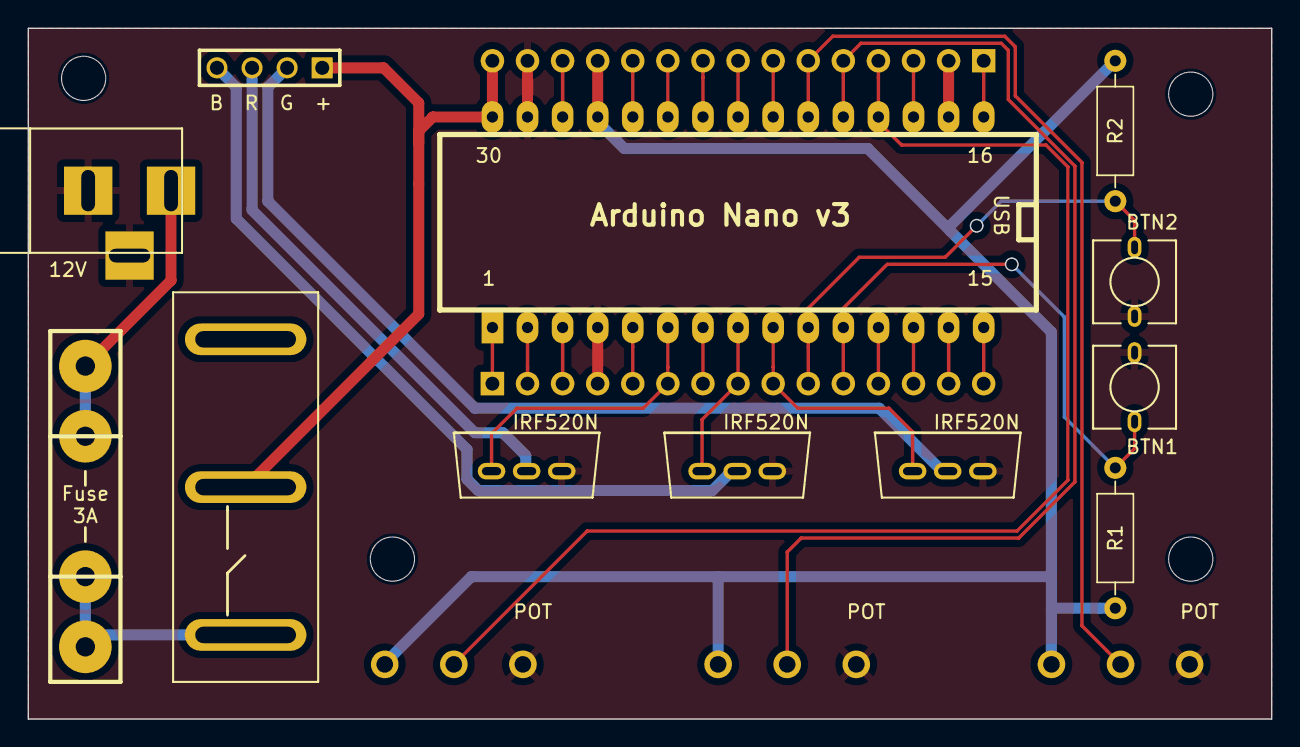
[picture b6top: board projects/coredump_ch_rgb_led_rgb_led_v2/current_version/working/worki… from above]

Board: 2 copper layers, 90.0 x 50.0 mm, 17 parts (0 on the bottom side), 34 nets.
